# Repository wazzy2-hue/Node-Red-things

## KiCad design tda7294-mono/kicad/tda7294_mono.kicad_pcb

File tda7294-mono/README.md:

# TDA7294 Mono Module — 4-layer "definitive" board (rev 1.0)

Redesign of the classic French TDA7294 module (as published on homemade-circuits.com) that has run
silently on the prototype for 12 years. Same circuit and values; new board.

Build two for a stereo pair (four for the 4-channel idea). One mono design = one fab order.

## Folder contents

| Path | What it is |
|---|---|
| `kicad/` | KiCad 7 project: `tda7294_mono.kicad_pro`, `.kicad_sch`, `.kicad_pcb`, plus `3dmodels/` (TDA7294 Multiwatt15 model) |
| `fab/gerbers/` | Gerbers (4 copper layers, mask, silk, outline) + separate PTH/NPTH Excellon drill files and drill maps |
| `fab/tda7294_mono_BOM.csv` | Grouped bill of materials |
| `fab/tda7294_mono_schematic.pdf` | Schematic |
| `renders/` | 3D renders and flat top/bottom views |
| `gen/` | Python that generates everything from one netlist (`circuit.py`) — edit there and re-run |

Opens in KiCad 7 or newer (KiCad 8/9 will offer to upgrade the files).

## Board

- 130 × 80 mm, 1.6 mm, 4 layers, **2 oz copper on all layers**, **ENIG**, black mask / white silk
- Heatsink along the top edge. The TDA7294 tab back face sits on the board edge.
- H1/H2 (top corners): M3 heatsink bracket holes. H3/H4: M3 standoffs.
  **These hole positions are placeholders.** Check them against your brackets before ordering.

### Stackup

| Layer | Use |
|---|---|
| F.Cu | All signal routing. PGND pour on the side arms; SGND pour over the signal area |
| In1 | Ground: SGND island under the small-signal parts, PGND everywhere else |
| In2 | +V plane, full board |
| B.Cu | −V plane, full board (one short MUTE track crosses under the IC) |

The supply rails each get a full 2 oz plane. The +V and −V planes are 0.2 mm apart, so they
also act as distributed decoupling.

### Grounding (carried over from the original)

- **SGND**: input ground, R2, C3, C1, C10, C12, and IC pins 1 and 4.
- **PGND**: rail cap centre point, C5/C6/C9/C11, speaker return, PSU 0 V.
- They meet at exactly one place: **NT1, the net tie marked STAR**, beside the 0 V pad.
  KiCad's DRC enforces this, so the separation can't be lost by an edit.
- The speaker output track runs over PGND, not over the signal-ground island.
- Feedback (R5) and bootstrap (C4) are taken directly at pin 14 by a thin sense track.
  The speaker current leaves pin 14 by a separate 2.5 mm track.

### Design rules

| Class | Nets | Track | Clearance | Via |
|---|---|---|---|---|
| Power | +V, −V, PGND, OUT | 2.5 mm | 0.6 mm | 1.6 / 0.8 mm |
| Default | everything else | 0.4 mm | 0.4 mm | 0.8 / 0.4 mm |

The 0.6 mm clearance covers 80 V rail-to-rail with margin.

Plane connections use wide thermal spokes (1.0–1.2 mm) so heavy copper can still be hand-soldered.
The exception is the IC's +V/−V/SGND pins, which have **solid** connections. Use a hot iron there.

IC holes are opened to 1.1 mm for the Multiwatt legs.

DRC: 0 violations, 0 unconnected. The schematic netlist, the PCB pads and `circuit.py` were
cross-checked and match.

## Changes from the original

- **Local rail caps.** Each rail gets 2 × Panasonic FC 2200 µF 50 V (EEU-FC1H222, 18 × 35.5 mm)
  instead of one 10 000 µF. That is 4400 µF of very low-ESR capacitance right at the chip.
  The FC series doesn't go to 10 000 µF at 50 V, and 35 V is too close to your ±33–35 V idle
  rails. Keep the big reservoir caps in the PSU, as you have now.
- **All electrolytics Panasonic FC, 50 V.**
  - C3, C4: 100 µF (EEU-FC1H101)
  - C1, C10: 10 µF (EEU-FC1H100L)
- **All resistors metal film 1 % 0.6 W.**
- **C4 polarity: + to pin 6 (BOOT).** This is marked on the silkscreen.
- **Optional RF input filter.**
  - R7 is fitted as a 0 Ω link by default. Change it to 100 Ω if you want the filter.
  - C12 (470 pF) is not fitted by default.
  - The original article noted a slight tendency to oscillate from high-impedance sources.
- **C9/C11 (10 µF film) kept.** The original author called them optional, but your proven build has them.
- **Wire pads along the bottom edge.** From left to right: +V, IN, GND, 0V, MUTE, SPK+, SPK−, −V.
  - Tie MUTE to +V for play, or to GND for standby.

## Fab order notes

- 4 layers, 1.6 mm, 2 oz outer and 2 oz inner copper, ENIG, black mask, white silk.
- Use the stackup in the board file or the house equivalent (prepreg 0.2 / core ~0.9 / prepreg 0.2).
- Check the minimum track/gap for 2 oz copper with your fab. This design uses 0.4/0.4 mm.

## Before ordering — please verify

1. **Heatsink bracket and standoff hole positions**, against your hardware.
2. **The Multiwatt15 lead form of the TDA7294s you have.** The footprint is the standard
   "StaggerOdd" vertical form, the same one the original board uses.
3. **The tab insulation kit**: mica or silpad, plus a shoulder washer. The tab is at −V.
4. **Print the top layer 1:1** (from the KiCad PCB editor) and lay your actual parts on it,
   especially the film caps. Their bodies vary by brand.

The 3D models are generic KiCad library models, recoloured where noted. The TDA7294 model is a
simplified outline built for this project.

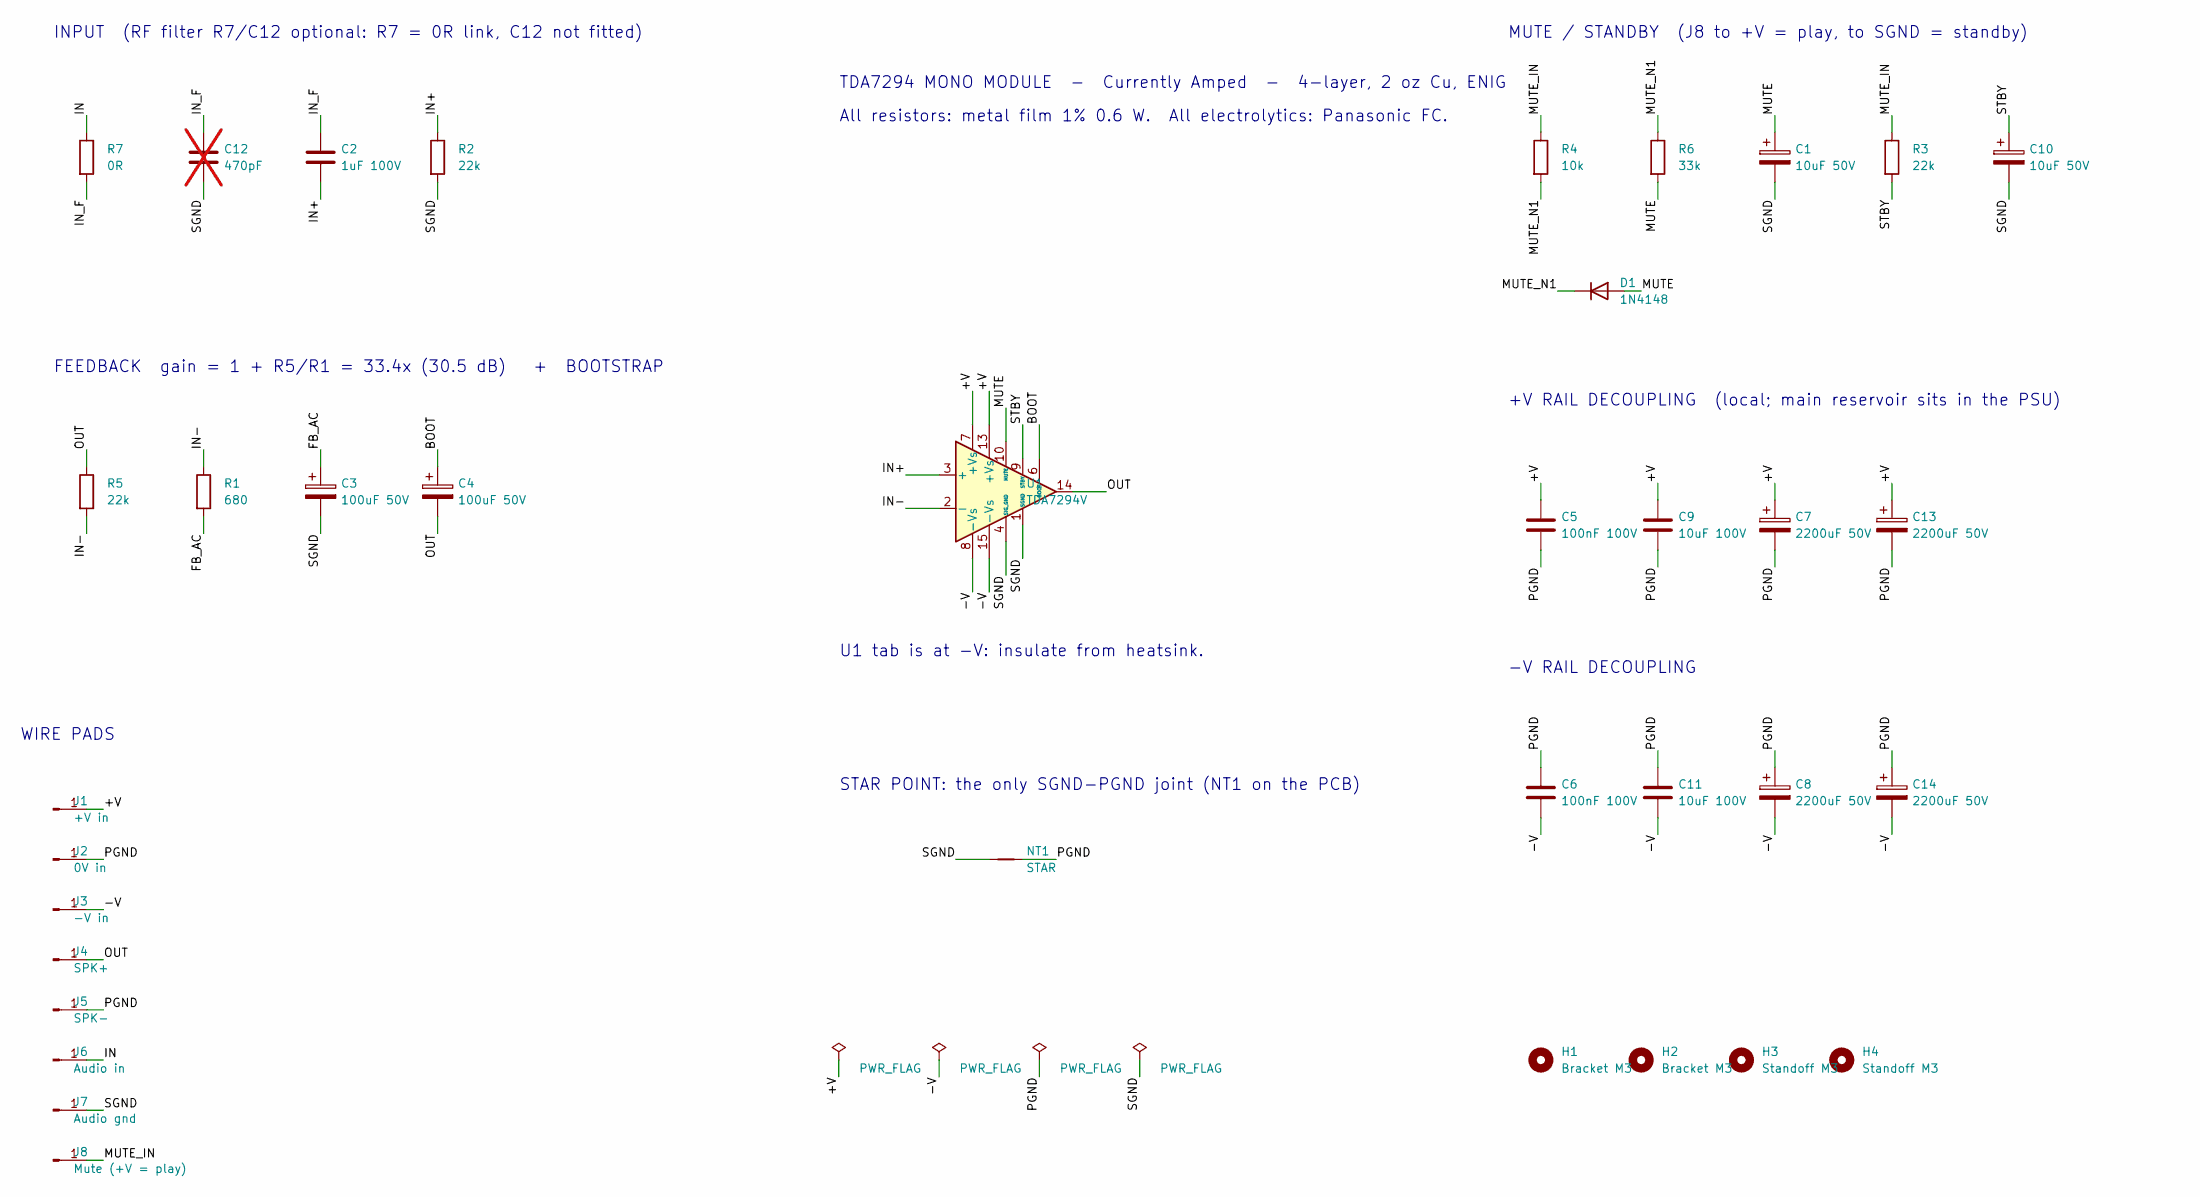
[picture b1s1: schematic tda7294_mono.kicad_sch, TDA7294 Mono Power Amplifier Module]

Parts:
C1, C10: 10uF 50V; CP_Radial_D5.0mm_P2.00mm; MPN EEU-FC1H100L
C2: 1uF 100V; C_Rect_L18.0mm_W8.0mm_P15.00mm_FKS3_FKP3
C3, C4: 100uF 50V; CP_Radial_D10.0mm_P5.00mm; MPN EEU-FC1H101
C5, C6: 100nF 100V; C_Rect_L7.2mm_W3.5mm_P5.00mm_FKS2_FKP2_MKS2_MKP2
C7, C8, C13, C14: 2200uF 50V; CP_Radial_D18.0mm_P7.50mm; MPN EEU-FC1H222
C9, C11: 10uF 100V; C_Rect_L31.5mm_W13.0mm_P27.50mm_MKS4
C12: 470pF; C_Rect_L7.2mm_W3.5mm_P5.00mm_FKS2_FKP2_MKS2_MKP2; not fitted
D1: 1N4148; D_DO-35_SOD27_P7.62mm_Horizontal
H1, H2: Bracket M3; MountingHole_3.2mm_M3
H3, H4: Standoff M3; MountingHole_3.2mm_M3
J1: +V in; SolderWire-1.5sqmm_1x01_D1.7mm_OD3.9mm
J2: 0V in; SolderWire-1.5sqmm_1x01_D1.7mm_OD3.9mm
J3: -V in; SolderWire-1.5sqmm_1x01_D1.7mm_OD3.9mm
J4: SPK+; SolderWire-1.5sqmm_1x01_D1.7mm_OD3.9mm
J5: SPK-; SolderWire-1.5sqmm_1x01_D1.7mm_OD3.9mm
J6: Audio in; SolderWire-0.5sqmm_1x01_D0.9mm_OD2.3mm
J7: Audio gnd; SolderWire-0.5sqmm_1x01_D0.9mm_OD2.3mm
J8: Mute (+V = play); SolderWire-0.5sqmm_1x01_D0.9mm_OD2.3mm
NT1: STAR; NetTie-2_SMD_Pad2.0mm
R1: 680; R_Axial_DIN0207_L6.3mm_D2.5mm_P10.16mm_Horizontal
R2, R3, R5: 22k; R_Axial_DIN0207_L6.3mm_D2.5mm_P10.16mm_Horizontal
R4: 10k; R_Axial_DIN0207_L6.3mm_D2.5mm_P10.16mm_Horizontal
R6: 33k; R_Axial_DIN0207_L6.3mm_D2.5mm_P10.16mm_Horizontal
R7: 0R; R_Axial_DIN0207_L6.3mm_D2.5mm_P10.16mm_Horizontal
U1: TDA7294V; TO-220-15_P2.54x2.54mm_StaggerOdd_Lead4.58mm_Vertical

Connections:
+V: C5.1, C7.1, C9.1, C13.1, J1.1, U1.7 (+Vs), U1.13 (+Vs)
-V: C6.2, C8.2, C11.2, C14.2, J3.1, U1.8 (-Vs), U1.15 (-Vs)
BOOT: C4.1, U1.6 (BOOT)
FB_AC: C3.1, R1.2
IN: J6.1, R7.1
IN+: C2.2, R2.1, U1.3 (+)
IN-: R1.1, R5.2, U1.2 (-)
IN_F: C2.1, C12.1, R7.2
MUTE: C1.1, D1.2 (A), R6.2, U1.10 (MUTE)
MUTE_IN: J8.1, R3.1, R4.1
MUTE_N1: D1.1 (K), R4.2, R6.1
OUT: C4.2, J4.1, R5.1, U1.14
PGND: C5.2, C6.1, C7.2, C8.1, C9.2, C11.1, C13.2, C14.1, J2.1, J5.1, NT1.2
SGND: C1.2, C3.2, C10.2, C12.2, J7.1, NT1.1, R2.2, U1.1 (SGND), U1.4 (SIG_GND)
STBY: C10.1, R3.2, U1.9 (STBY)

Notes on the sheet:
INPUT (RF filter R7/C12 optional: R7 = 0R link, C12 not fitted)
FEEDBACK gain = 1 + R5/R1 = 33.4x (30.5 dB) + BOOTSTRAP
MUTE / STANDBY (J8 to +V = play, to SGND = standby)
+V RAIL DECOUPLING (local; main reservoir sits in the PSU)
-V RAIL DECOUPLING
WIRE PADS
STAR POINT: the only SGND-PGND joint (NT1 on the PCB)
TDA7294 MONO MODULE - Currently Amped - 4-layer, 2 oz Cu, ENIG
All resistors: metal film 1% 0.6 W. All electrolytics: Panasonic FC.
U1 tab is at -V: insulate from heatsink.

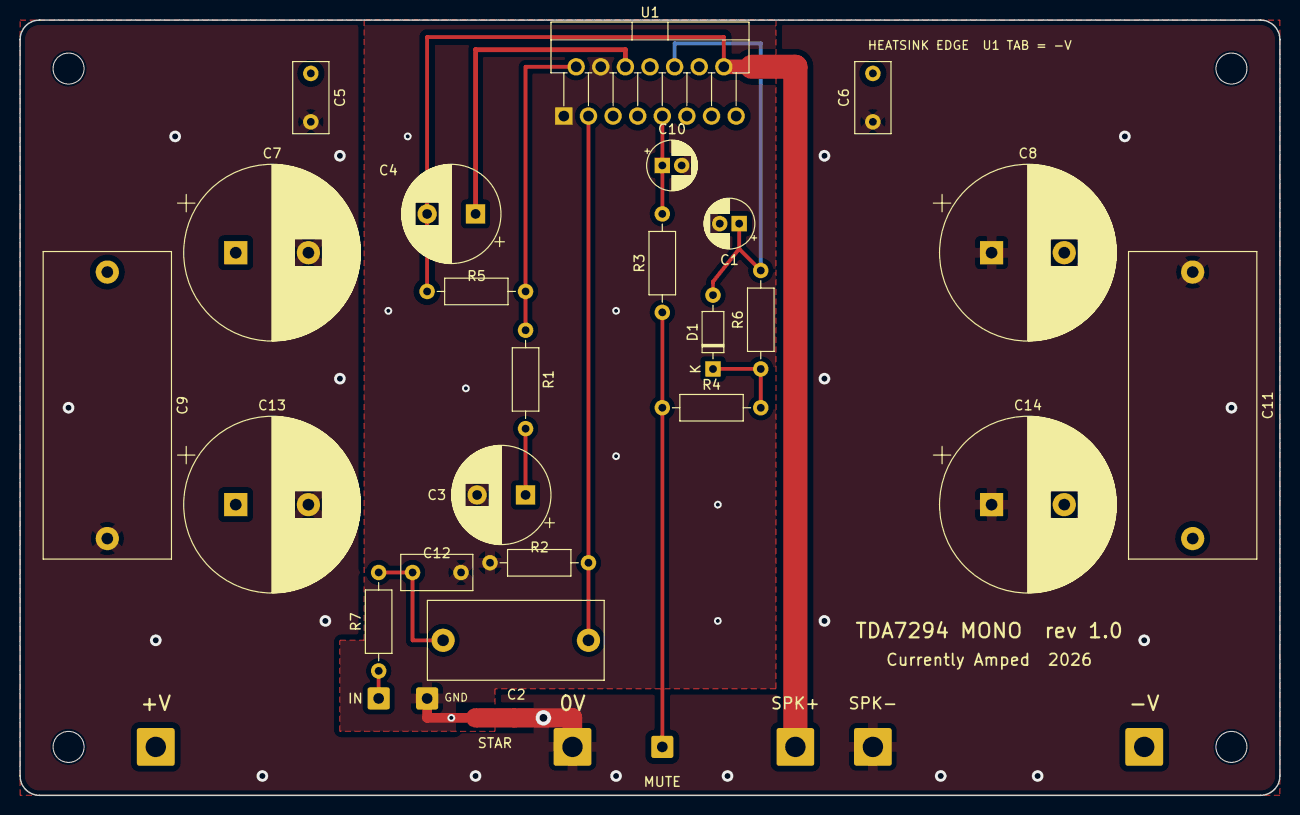
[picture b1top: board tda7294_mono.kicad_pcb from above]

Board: 4 copper layers, 130.0 x 80.0 mm, 36 parts (0 on the bottom side), 15 nets.

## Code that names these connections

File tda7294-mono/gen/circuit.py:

"""Single source of truth for the TDA7294 mono module.

Every part: reference -> (lib_id, value, footprint, {pin: net}, extra fields).
Both the schematic and the PCB generator read this, so they cannot drift.
"""

FP = {
    "U":      "Package_TO_SOT_THT:TO-220-15_P2.54x2.54mm_StaggerOdd_Lead4.58mm_Vertical",
    "R":      "Resistor_THT:R_Axial_DIN0207_L6.3mm_D2.5mm_P10.16mm_Horizontal",
    "D":      "Diode_THT:D_DO-35_SOD27_P7.62mm_Horizontal",
    "FC18":   "Capacitor_THT:CP_Radial_D18.0mm_P7.50mm",
    "FC10":   "Capacitor_THT:CP_Radial_D10.0mm_P5.00mm",
    "FC5":    "Capacitor_THT:CP_Radial_D5.0mm_P2.00mm",
    "FILM10": "Capacitor_THT:C_Rect_L31.5mm_W13.0mm_P27.50mm_MKS4",
    "FILM1":  "Capacitor_THT:C_Rect_L18.0mm_W8.0mm_P15.00mm_FKS3_FKP3",
    "FILM01": "Capacitor_THT:C_Rect_L7.2mm_W3.5mm_P5.00mm_FKS2_FKP2_MKS2_MKP2",
    "PWRPAD": "Connector_Wire:SolderWire-1.5sqmm_1x01_D1.7mm_OD3.9mm",
    "SIGPAD": "Connector_Wire:SolderWire-0.5sqmm_1x01_D0.9mm_OD2.3mm",
    "TIE":    "NetTie:NetTie-2_SMD_Pad2.0mm",
    "HOLE":   "MountingHole:MountingHole_3.2mm_M3",
}

MF = "Metal film 1% 0.6W"
FC = "Panasonic FC"

# ref: (lib_id, value, fp_key, pins, fields)
PARTS = {
    "U1":  ("Amplifier_Audio:TDA7294", "TDA7294V", "U",
            {1: "SGND", 2: "IN-", 3: "IN+", 4: "SGND", 6: "BOOT", 7: "+V", 8: "-V",
             9: "STBY", 10: "MUTE", 13: "+V", 14: "OUT", 15: "-V"},
            {"Note": "Tab = -V. Insulate from heatsink (silpad + shoulder washer)"}),
    # --- gain / feedback ---------------------------------------------------
    "R1":  ("Device:R", "680", "R", {1: "IN-", 2: "FB_AC"}, {"Type": MF}),
    "R5":  ("Device:R", "22k", "R", {1: "OUT", 2: "IN-"}, {"Type": MF}),
    "C3":  ("Device:C_Polarized", "100uF 50V", "FC10", {1: "FB_AC", 2: "SGND"},
            {"Type": FC, "MPN": "EEU-FC1H101"}),
    # --- input ---------------------------------------------------------------
    "R7":  ("Device:R", "0R", "R", {1: "IN", 2: "IN_F"},
            {"Type": "0 ohm link (100R option for RF filter)"}),
    "C12": ("Device:C", "470pF", "FILM01", {1: "IN_F", 2: "SGND"},
            {"Type": "C0G/film, DO NOT FIT (RF filter option)", "DNP": "yes"}),
    "C2":  ("Device:C", "1uF 100V", "FILM1", {1: "IN_F", 2: "IN+"},
            {"Type": "MKP/MKS film, P15mm"}),
    "R2":  ("Device:R", "22k", "R", {1: "IN+", 2: "SGND"}, {"Type": MF}),
    # --- bootstrap -----------------------------------------------------------
    "C4":  ("Device:C_Polarized", "100uF 50V", "FC10", {1: "BOOT", 2: "OUT"},
            {"Type": FC, "MPN": "EEU-FC1H101", "Note": "+ to pin 6 (BOOT)"}),
    # --- mute / standby timing ----------------------------------------------
    "R4":  ("Device:R", "10k", "R", {1: "MUTE_IN", 2: "MUTE_N1"}, {"Type": MF}),
    "R6":  ("Device:R", "33k", "R", {1: "MUTE_N1", 2: "MUTE"}, {"Type": MF}),
    "D1":  ("Device:D", "1N4148", "D", {1: "MUTE_N1", 2: "MUTE"}, {}),  # 1=K 2=A
    "C1":  ("Device:C_Polarized", "10uF 50V", "FC5", {1: "MUTE", 2: "SGND"},
            {"Type": FC, "MPN": "EEU-FC1H100L"}),
    "R3":  ("Device:R", "22k", "R", {1: "MUTE_IN", 2: "STBY"}, {"Type": MF}),
    "C10": ("Device:C_Polarized", "10uF 50V", "FC5", {1: "STBY", 2: "SGND"},
            {"Type": FC, "MPN": "EEU-FC1H100L"}),
    # --- +V rail -------------------------------------------------------------
    "C5":  ("Device:C", "100nF 100V", "FILM01", {1: "+V", 2: "PGND"}, {"Type": "MKS/MKP film"}),
    "C9":  ("Device:C", "10uF 100V", "FILM10", {1: "+V", 2: "PGND"},
            {"Type": "MKS4 film (optional, as original)"}),
    "C7": ("Device:C_Polarized", "2200uF 50V", "FC18", {1: "+V", 2: "PGND"},
            {"Type": FC, "MPN": "EEU-FC1H222"}),
    "C13": ("Device:C_Polarized", "2200uF 50V", "FC18", {1: "+V", 2: "PGND"},
            {"Type": FC, "MPN": "EEU-FC1H222"}),
    # --- -V rail -------------------------------------------------------------
    "C6":  ("Device:C", "100nF 100V", "FILM01", {1: "PGND", 2: "-V"}, {"Type": "MKS/MKP film"}),
    "C11": ("Device:C", "10uF 100V", "FILM10", {1: "PGND", 2: "-V"},
            {"Type": "MKS4 film (optional, as original)"}),
    "C8": ("Device:C_Polarized", "2200uF 50V", "FC18", {1: "PGND", 2: "-V"},
            {"Type": FC, "MPN": "EEU-FC1H222"}),
    "C14": ("Device:C_Polarized", "2200uF 50V", "FC18", {1: "PGND", 2: "-V"},
            {"Type": FC, "MPN": "EEU-FC1H222"}),
    # --- star point ------------------------------------------------------------
    "NT1": ("Device:NetTie_2", "STAR", "TIE", {1: "SGND", 2: "PGND"}, {}),
    # --- wire pads -------------------------------------------------------------
    "J1":  ("Connector:Conn_01x01_Pin", "+V in", "PWRPAD", {1: "+V"}, {}),
    "J2":  ("Connector:Conn_01x01_Pin", "0V in", "PWRPAD", {1: "PGND"}, {}),
    "J3":  ("Connector:Conn_01x01_Pin", "-V in", "PWRPAD", {1: "-V"}, {}),
    "J4":  ("Connector:Conn_01x01_Pin", "SPK+", "PWRPAD", {1: "OUT"}, {}),
    "J5":  ("Connector:Conn_01x01_Pin", "SPK-", "PWRPAD", {1: "PGND"}, {}),
    "J6":  ("Connector:Conn_01x01_Pin", "Audio in", "SIGPAD", {1: "IN"}, {}),
    "J7":  ("Connector:Conn_01x01_Pin", "Audio gnd", "SIGPAD", {1: "SGND"}, {}),
    "J8":  ("Connector:Conn_01x01_Pin", "Mute (+V = play)", "SIGPAD", {1: "MUTE_IN"}, {}),
    # --- mechanical --------------------------------------------------------------
    "H1":  ("Mechanical:MountingHole", "Bracket M3", "HOLE", {}, {}),
    "H2":  ("Mechanical:MountingHole", "Bracket M3", "HOLE", {}, {}),
    "H3":  ("Mechanical:MountingHole", "Standoff M3", "HOLE", {}, {}),
    "H4":  ("Mechanical:MountingHole", "Standoff M3", "HOLE", {}, {}),
}

POWER_NETS = {"+V", "-V", "PGND", "OUT"}


def nets():
    out = {}
    for ref, (_, _, _, pins, _) in PARTS.items():
        for pin, net in pins.items():
            out.setdefault(net, []).append((ref, str(pin)))
    return out
